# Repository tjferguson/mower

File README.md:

# General Information

The purpose of this project is to turn a bunch of ardiuno + FPV electronics into a fully functional FPV lawn mower capable of handling my side lawn; this particular lawn happens to have between a 15 and 30% grade in different areas, and as evidenced by the missing tip of my right grand toe, is fairly dangerous to mow.   

## Parts List

### Pre-Built
* Arduino Uno
* 2x MegaMoto Motor Control (H-Bridge)
* RS81 FrSky receiver
* Foxeer 1200TVL Razer Nano FPV Camera
* Mateksys VTX-HV video transmitter

### Single Components

#### Inverter
* 2x 10k Resisters
* 1x 2N3904 Transitor
* PCB

#### Power Rail
* 4x 12V 7.5AH F2 SLA Batteries 

#### Drive Configuration
* 2x 24V 350W MY1016 Electric Motor with 11 Tooth #25 Chain Sprocket
*

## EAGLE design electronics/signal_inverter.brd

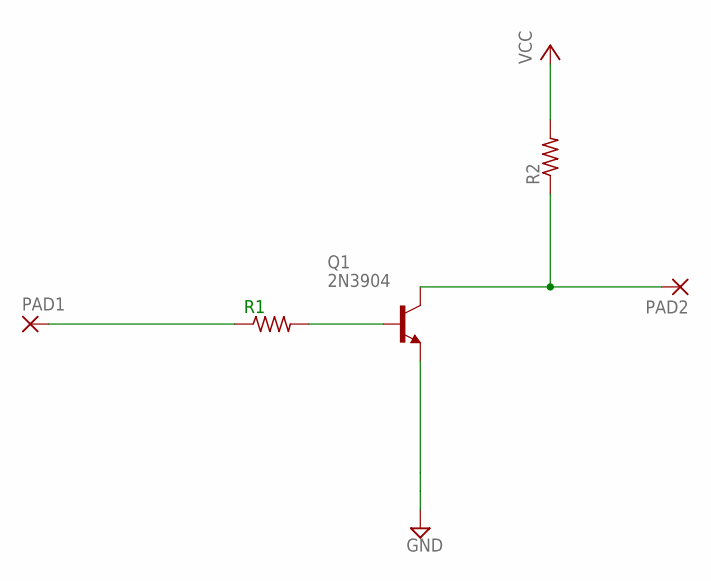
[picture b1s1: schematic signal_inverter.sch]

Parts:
PAD1, PAD2: 2,15/1,0
Q1: 2N3904; TO92
R1, R2: R-US_0204/7; 0204/7

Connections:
GND: Q1.3 (E)
unnamed: Q1.2 (B), R1.2
unnamed: PAD2.1, Q1.1 (C), R2.1
unnamed: PAD1.1, R1.1
VCC: R2.2

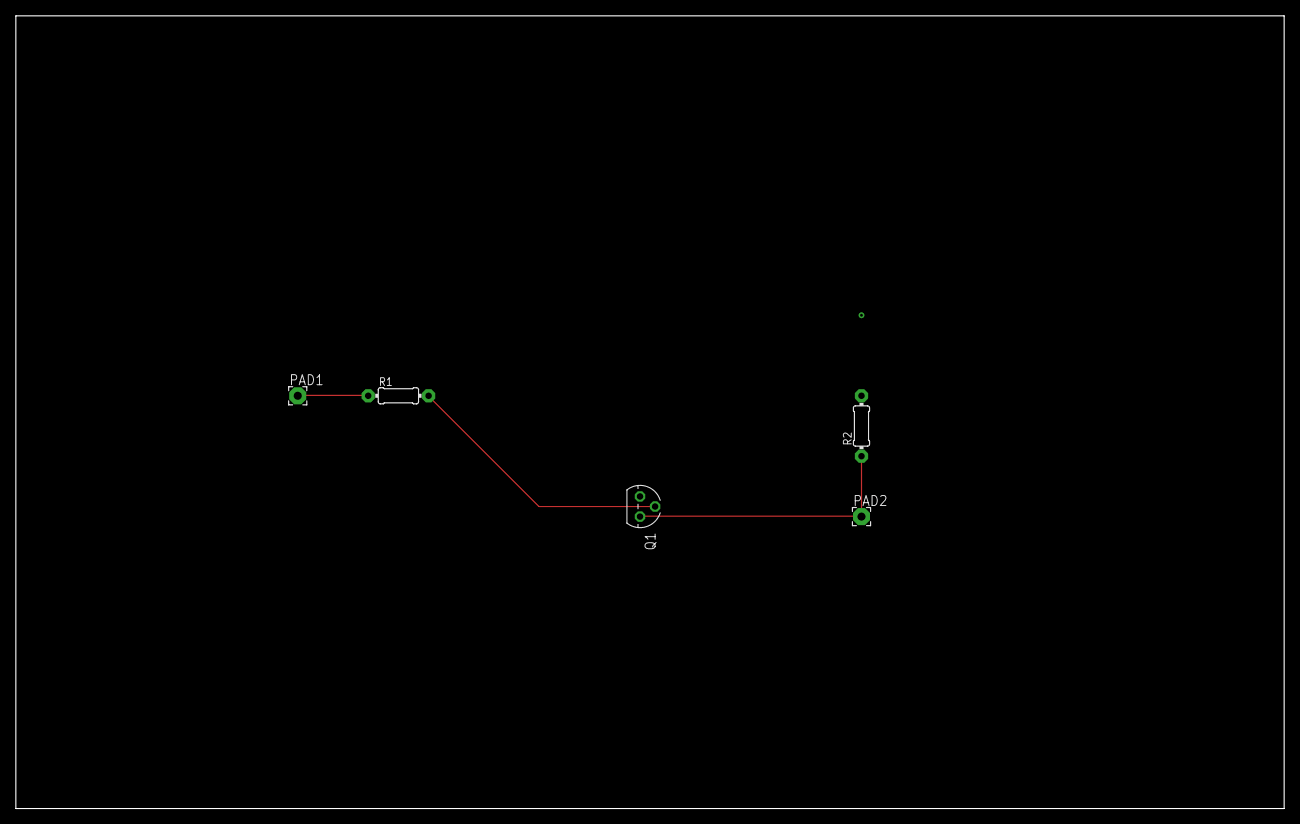
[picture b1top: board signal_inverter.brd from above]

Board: 2 copper layers, 160.0 x 100.0 mm, 5 parts (0 on the bottom side), 3 nets.

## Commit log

2022-03-14 Updated cpp to read when controller is connected or not.
2022-03-16 Updated to include checks for control changes
2022-03-25 updated to allow controlling of ardiuno
